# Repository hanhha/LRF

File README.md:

# LFR

A simple DIY laser range finder.

This is a very simple DIY laser range finder. For fast prototyping, I uses a Raspberry Pi 1 board with a web cam, a cheap laser diode (<5mW, I think) and some 3d printed bars to align the parts.

## Folder organization:

**src** - *all source code*

**eltr** - *all electric/electronic stuffs*

**model** - *all models of frame, mount, ... that would be 3d printed*

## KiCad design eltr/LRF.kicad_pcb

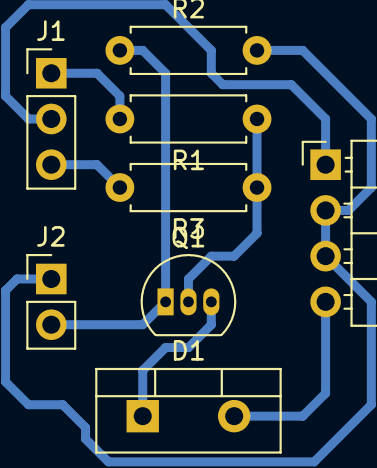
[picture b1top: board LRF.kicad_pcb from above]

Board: 2 copper layers, 8 parts (0 on the bottom side), 8 nets.

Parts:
D1: Laser diode; TO-220-2_Vertical
J1: CONN_01X03_MALE; Pin_Header_Straight_1x03_Pitch2.54mm
J2: CONN_01X02_MALE; Pin_Header_Straight_1x02_Pitch2.54mm
P1: CONN_01X04; Pin_Header_Angled_1x04_Pitch2.54mm
Q1: PN2222A; TO-92_Inline_Narrow_Oval
R1: 100; R_Axial_DIN0207_L6.3mm_D2.5mm_P7.62mm_Horizontal
R2: 10K; R_Axial_DIN0207_L6.3mm_D2.5mm_P7.62mm_Horizontal
R3: 1K; R_Axial_DIN0207_L6.3mm_D2.5mm_P7.62mm_Horizontal

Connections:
+5V: D1.2, P1.4
GND: J2.1, P1.2, P1.3, R2.2
GPIO: J1.2, P1.1
unnamed: D1.1, Q1.3
unnamed: J1.1, R1.2
unnamed: J1.3, R3.2
unnamed: J2.2, Q1.1, R2.1
unnamed: Q1.2, R1.1, R3.1

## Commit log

2017-08-13 Added the circuit to control laser diode using RPI GPIO pin
2017-08-13 Add model for mounting camera, laser diode
2017-12-12 Adding source to test camera module
2017-12-12 Adding info to show up
2017-12-13 Control laser
2017-12-18 Detect laser point
2017-12-27 Calculating distance with temporary parameters
2017-12-27 Keep implementing
2018-03-03 Try in noon condition
2018-03-04 Adding no pygame script
2018-10-18 Cleaning up
